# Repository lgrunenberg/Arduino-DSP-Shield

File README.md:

Arduino-DSP-Shield
==================

Eagle files for a DSP Shield to be used with Arduino Duemilanove and others.

It utilizes the Analog Devices ADAU1701 DSP IC. It also has solder pads for an EEPROM that can be used to store configurations and allow the ADAU to boot automatically when not connected to an Arduino.

Inputs and outputs are brought out to a pin header as I thought it would be more convenient than having TRS jacks directly on the board.

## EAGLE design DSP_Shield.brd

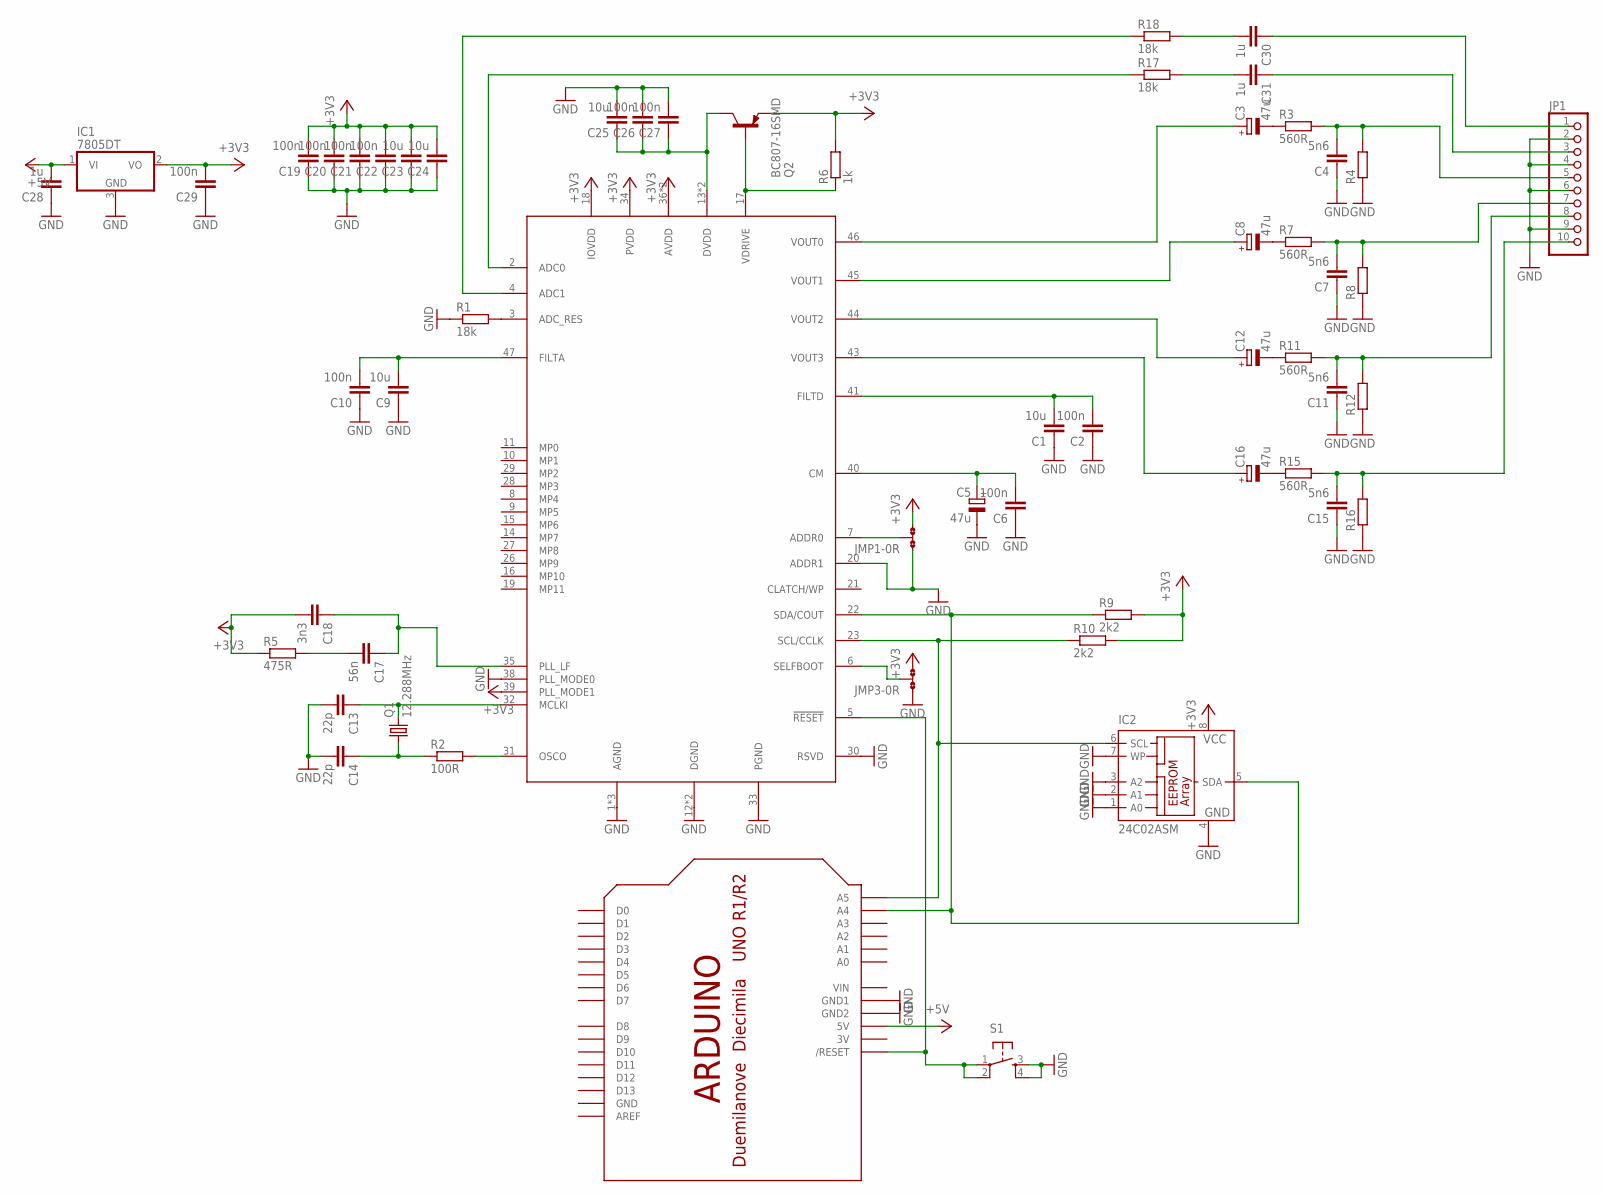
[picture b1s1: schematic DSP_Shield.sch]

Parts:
C1, C9, C23, C24, C25: 10u; C0805
C2, C6, C10, C19, C20, C21, C22, C26, C27, C29: 100n; C0805
C3, C8, C12, C16: 47u; PANASONIC_D
C4, C7, C11, C15: 5n6; C0805
C5: 47u; PANASONIC_B
C13, C14: 22p; C0805
C17: 56n; C0805
C18: 3n3; C0805
C28, C30, C31: 1u; C0805
IC1: 7805DT; TO252
IC2: 24C02ASM; SO-08M
JMP1, JMP3: 0R-JUMPA; A0R-JMP
JP1: PINHD-1X10/90; 1X10/90
Q1: 12.288MHz; HC49UP
Q2: BC807-16SMD; SOT23-BEC
R1, R17, R18: 18k; R0805
R2: 100R; R0805
R3, R7, R11, R15: 560R; R0805
R4, R8, R12, R16: R-EU_R0805; R0805
R5: 475R; R0805
R6: 1k; R0805
R9, R10: 2k2; R0805
S1: TAC_SWITCHSMD; TACTILE_SWITCH_SMD
U$1: ARDUINO-NODIM
U$2: ADAU1701; TQFP48

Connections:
3V: U$1.3V
+3V3: C18.2, C19.2, C20.2, C21.2, C22.2, C23.2, C24.2, C29.2, IC1.2 (VO), IC2.8 (VCC), JMP1.3, JMP3.3, Q2.E, R5.1, R6.2, R9.2, R10.2, U$2.18 (IOVDD), U$2.34 (PVDD), U$2.36 (AVDD), U$2.39 (PLL_MODE1), U$2.48 (AVDD)
+5V: C28.2, IC1.1 (VI), U$1.5V
GND: C1.1, C2.1, C4.1, C5.-, C6.1, C7.1, C9.1, C10.1, C11.1, C13.2, C14.2, C15.1, C19.1, C20.1, C21.1, C22.1, C23.1, C24.1, C25.2, C26.2, C27.2, C28.1, C29.1, IC1.3 (GND), IC2.1 (A0), IC2.2 (A1), IC2.3 (A2), IC2.4 (GND), IC2.7 (WP), JMP1.1, JMP3.1, JP1.2, JP1.4, JP1.6, JP1.9, R1.1, R4.1, R8.1, R12.1, R16.1, S1.3, S1.4, U$1.GND, U$1.GND1, U$1.GND2, U$2.1 (AGND), U$2.12 (DGND), U$2.20 (ADDR1), U$2.25 (DGND), U$2.30 (RSVD), U$2.33 (PGND), U$2.37 (AGND), U$2.38 (PLL_MODE0), U$2.42 (AGND)
unnamed: R2.2, U$2.31 (OSCO)
unnamed: R1.2, U$2.3 (ADC_RES)
unnamed: C1.2, C2.2, U$2.41 (FILTD)
unnamed: C3.-, R3.1
unnamed: C4.2, JP1.5, R3.2, R4.2
unnamed: C14.1, Q1.1, R2.1
unnamed: C5.+, C6.2, U$2.40 (CM)
unnamed: C9.2, C10.2, U$2.47 (FILTA)
unnamed: C8.-, R7.1
unnamed: C7.2, JP1.7, R7.2, R8.2
unnamed: C13.1, Q1.2, U$2.32 (MCLKI)
unnamed: R18.1, U$2.4 (ADC1)
unnamed: C17.2, R5.2
unnamed: C12.-, R11.1
unnamed: C11.2, JP1.8, R11.2, R12.2
unnamed: C16.+, U$2.43 (VOUT3)
unnamed: C17.1, C18.1, U$2.35 (PLL_LF)
unnamed: JMP1.2, U$2.7 (ADDR0)
unnamed: C16.-, R15.1
unnamed: C15.2, JP1.10, R15.2, R16.2
unnamed: IC2.6 (SCL), R10.1, U$1.A5, U$2.23 (SCL/CCLK)
unnamed: IC2.5 (SDA), R9.1, U$1.A4, U$2.22 (SDA/COUT)
unnamed: C12.+, U$2.44 (VOUT2)
unnamed: C8.+, U$2.45 (VOUT1)
unnamed: C3.+, U$2.46 (VOUT0)
unnamed: S1.1, S1.2, U$1.RESET (/RESET), U$2.5 (!RESET)
unnamed: C31.1, JP1.3
unnamed: C30.1, JP1.1
unnamed: R17.1, U$2.2 (ADC0)
unnamed: C31.2, R17.2
unnamed: C25.1, C26.1, C27.1, Q2.C, U$2.13 (DVDD), U$2.24 (DVDD)
unnamed: Q2.B, R6.1, U$2.17 (VDRIVE)
unnamed: C30.2, R18.2
unnamed: JMP3.2, U$2.6 (SELFBOOT)
VIN: U$1.VIN

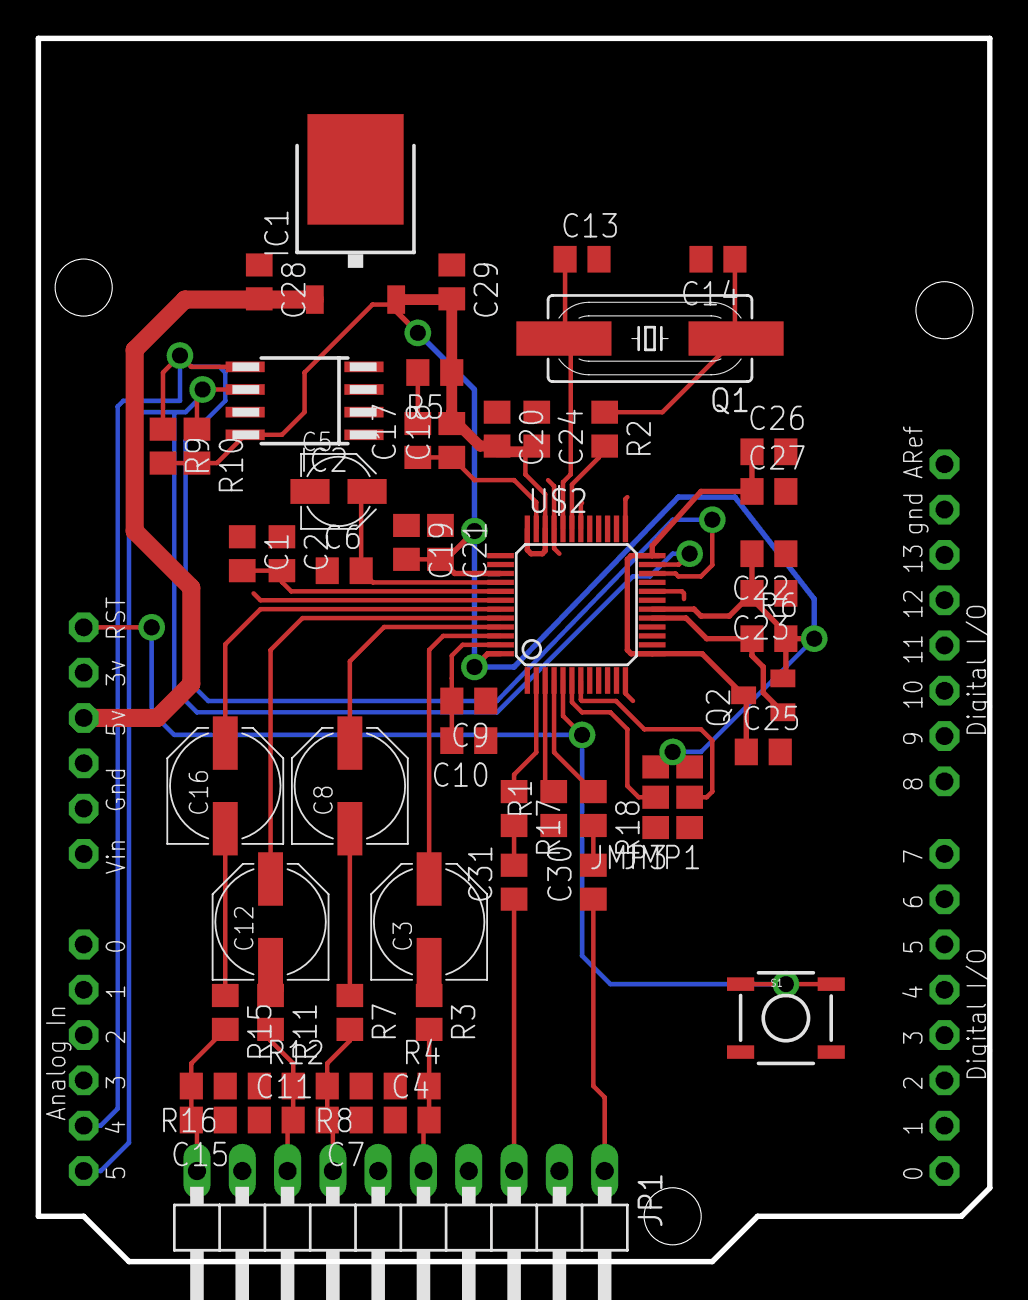
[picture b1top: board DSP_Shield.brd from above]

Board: 2 copper layers, 53.3 x 68.6 mm, 57 parts (0 on the bottom side), 37 nets.

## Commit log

2014-01-04 Create LICENSE
